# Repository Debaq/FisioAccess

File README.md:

# FisioAccess

Software para la toma de electrocardiograma

## Description

This project was created with PySide6 and Python.

## Author

- **Vanessa**
- Email: vanessauribe858@gmail.com
- Organization: Uach

## Version

1.0.0

## License

This project is under the MIT license.

## Project Structure

```
src/
├── config/        # Configuration files
├── ui/            # User interface components
│   ├── dialogs/   # Dialog windows
│   └── views/     # View components
├── models/        # Data models
└── utils/         # Utility functions

resources/
├── images/        # Images and icons
├── styles/        # Style sheets
├── icons/         # Application icons
└── translations/  # Language files
    ├── es.ts     # Spanish translation source
    ├── es.qm     # Compiled Spanish translation
    ├── en.ts     # English translation source
    └── en.qm     # Compiled English translation
```

## Requirements

- Python 3.12+
- PySide6
- Qt6 tools (for translations)
- Other dependencies in requirements.txt

## Installation

1. Clone the repository
2. Activate virtual environment: `source activate_env.sh`
3. Install dependencies: `pip install -r requirements.txt`
4. Compile translations: `./compile_translations.sh`

## Translations

### Adding a New Language

1. Create a new translation file (example for French):
   ```bash
   # Create fr.ts file in resources/translations/
   <?xml version="1.0" encoding="utf-8"?>
   <!DOCTYPE TS>
   <TS version="2.1" language="fr">
   <context>
       <name>MainWindow</name>
       <message>
           <source>Welcome to {}</source>
           <translation>Bienvenue à {}</translation>
       </message>
       <!-- Add more translations here -->
   </context>
   </TS>
   ```

2. Add the new language to compile_translations.sh:
   ```bash
    resources/translations/fr.ts -qm resources/translations/fr.qm
   ```

3. Compile translations:
   ```bash
   ./compile_translations.sh
   ```

### Creating Translation Files

The easiest way to create translation files is using Qt Linguist:

1. Install Qt6 Linguist:
   - Ubuntu/Debian: `sudo apt-get install qt6-tools-dev`
   - Fedora: `sudo dnf install qt6-linguist`
   - Arch: `sudo pacman -S qt6-tools`

2. Generate translation files:
   ```bash
   # Create/update .ts files
   lupdate-qt6 src/ -ts resources/translations/es.ts
   ```

3. Edit translations using Qt Linguist:
   ```bash
   linguist-qt6 resources/translations/es.ts
   ```

4. Compile translations:
   ```bash
   ./compile_translations.sh
   ```

## Building

To compile the project, run:

```bash
./compile.sh
```

## Usage

To run in development mode:

```bash
python src/main.py
```

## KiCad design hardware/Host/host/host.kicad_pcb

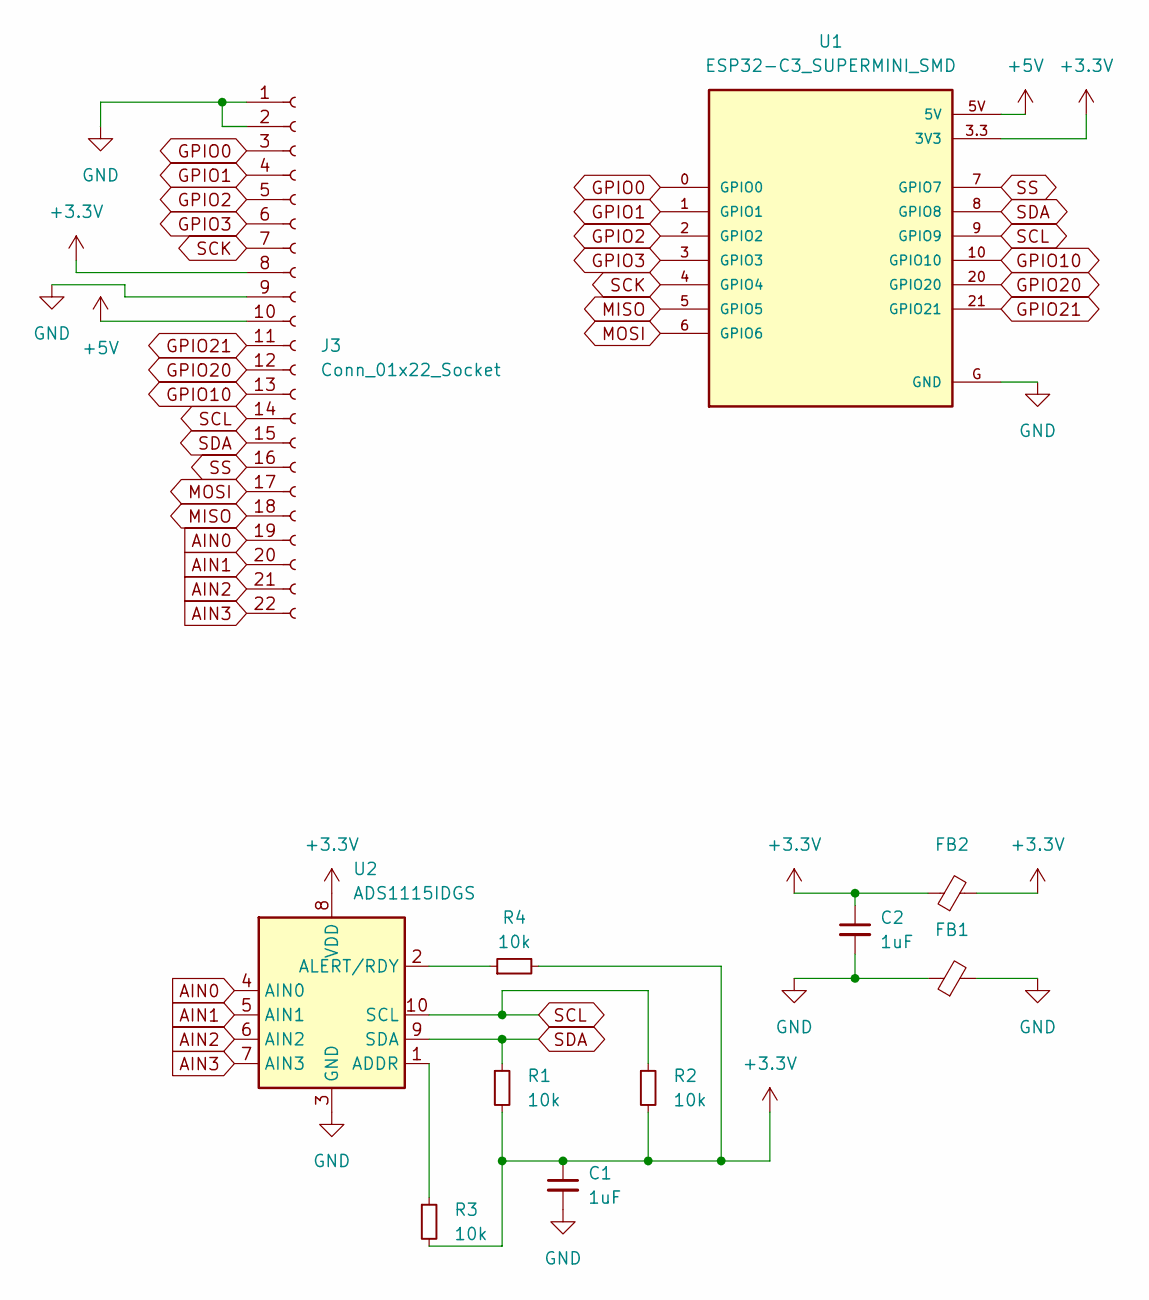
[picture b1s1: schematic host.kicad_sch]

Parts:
C1, C2: 1uF; C_1206_3216Metric_Pad1.33x1.80mm_HandSolder
FB1, FB2: L_1206_3216Metric_Pad1.22x1.90mm_HandSolder
J3: Conn_01x22_Socket; conn_board_host
R1, R2, R3, R4: 10k; R_1206_3216Metric_Pad1.30x1.75mm_HandSolder
U1: ESP32-C3_SUPERMINI_SMD; MODULE_ESP32-C3_SUPERMINI
U2: ADS1115IDGS; TSSOP-10_3x3mm_P0.5mm

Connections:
+3.3V: C1.1, C2.1, FB2.1, FB2.2, J3.8, R1.2, R2.2, R3.2, R4.2, U1.3.3 (3V3), U2.8 (VDD)
+5V: J3.10, U1.5V
AIN0: J3.19, U2.4 (AIN0)
AIN1: J3.20, U2.5 (AIN1)
AIN2: J3.21, U2.6 (AIN2)
AIN3: J3.22, U2.7 (AIN3)
GND: C1.2, C2.2, FB1.1, FB1.2, J3.1, J3.2, J3.9, U1.G (GND), U2.3 (GND)
GPIO0: J3.3, U1.0 (GPIO0)
GPIO1: J3.4, U1.1 (GPIO1)
GPIO2: J3.5, U1.2 (GPIO2)
GPIO3: J3.6, U1.3 (GPIO3)
GPIO10: J3.13, U1.10 (GPIO10)
GPIO20: J3.12, U1.20 (GPIO20)
GPIO21: J3.11, U1.21 (GPIO21)
MISO: J3.18, U1.5 (GPIO5)
MOSI: J3.17, U1.6 (GPIO6)
unnamed: R3.1, U2.1 (ADDR)
unnamed: R4.1, U2.2 (ALERT/RDY)
SCK: J3.7, U1.4 (GPIO4)
SCL: J3.14, R2.1, U1.9 (GPIO9), U2.10 (SCL)
SDA: J3.15, R1.1, U1.8 (GPIO8), U2.9 (SDA)
SS: J3.16, U1.7 (GPIO7)

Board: 2 copper layers, 11 parts (0 on the bottom side), 22 nets, no tracks yet.

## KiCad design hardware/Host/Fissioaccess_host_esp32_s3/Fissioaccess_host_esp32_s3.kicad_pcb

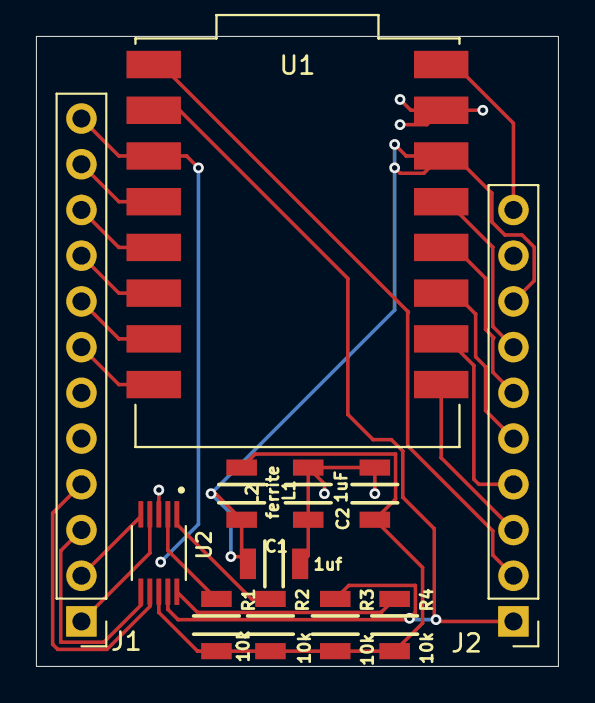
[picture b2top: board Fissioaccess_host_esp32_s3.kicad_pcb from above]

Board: 2 copper layers, 29.0 x 35.0 mm, 12 parts (0 on the bottom side), 23 nets.

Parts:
C1: 1uf; C_1206
C2: 1uF; C_1206
J1: PINHD_1x12; PinHeader_1x12_P2.54mm_Vertical
J2: PINHD_1x10; PinHeader_1x10_P2.54mm_Vertical
L1, L2: ferrite; C_1206
R1, R2, R3, R4: 10k; C_1206
U1: ESP32-C3; MODULE_ESP32-C3_SUPERMINI
U2: ADS; SOP50P490X110-10N

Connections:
+5V: J2.10, U1.5V
AIN0: J1.1, U2.4 (AIN0)
AIN1: J1.2, U2.5 (AIN1)
AIN2: J1.3, U2.6 (AIN2)
AIN3: J1.4, U2.7 (AIN3)
GND: C1.2, C2.2, J2.9, L1.1 (+), L1.2 (-), U1.G (GND), U2.3 (GND)
GPIO0: J2.3, U1.0 (GPIO0)
GPIO1: J2.4, U1.1 (GPIO1)
GPIO2: J2.5, U1.2 (GPIO2)
GPIO3: J2.6, U1.3 (GPIO3)
GPIO4: J2.7, U1.4 (GPIO4)
GPIO5: J2.2, U1.5 (GPIO5)
GPIO6: J2.1, R3.1, U1.6 (GPIO6), U2.9 (SDA)
GPIO7: J1.12, R4.1, U1.7 (GPIO7), U2.10 (SCL)
GPIO8: J1.11, U1.8 (GPIO8)
GPIO9: J1.10, U1.9 (GPIO9)
GPIO10: J1.9, U1.10 (GPIO10)
GPIO20: J1.8, U1.20 (GPIO20)
GPIO21: J1.7, U1.21 (GPIO21)
unnamed: R2.1, U2.1 (ADDR)
unnamed: R1.1, U2.2 (ALERT/RDY)
VCC: C1.1, J2.8, L2.2 (-), U1.3.3 (3V3)
VCC B: C2.1, L2.1 (+), R1.2, R2.2, R3.2, R4.2, U2.8 (VDD)

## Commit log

2024-07-25 cambios
2024-07-25 upgrade kivymd
2024-07-26 nuevos_para otra versión
2024-08-03 Add rst
2024-08-03 update help screen
2024-08-10 update rst and images
2024-08-12 mejoras para graficas
2024-08-13 rst update
2024-09-03 nuevo grafico
2024-09-10 nueva versión
2024-09-10 cambios v3
2024-09-18 logo
2024-09-18 cambios en la versión
2024-09-18 change in icons
2024-09-18 color in button
2024-09-19 cambios para funcionamiento del grafico
2024-09-20 marcadores
2024-09-21 funcionamiento correcto del toolbar
2024-09-21 limpieza de codigo pep8
2024-09-24 limpieza
2024-09-30 Create tree
2024-09-30 verificador de fb
2024-09-30 cierre fb
2024-09-30 firmware
2024-09-30 temp
2024-10-09 funcionamiento_puerto Serial
2024-10-09 cambios para serial
2024-10-09 ajuste de label serial
2024-10-09 funcionamiento en bind
2024-10-10 cambios otros
2024-10-14 connect_to_wifi
2024-10-14 cambio para web
2024-10-14 mejoras en el marcaje
2024-10-15 avance en la calibración
2025-03-31 Remove
2025-03-31 cambios menores
2025-03-31 cambios a versión piloto
    hemos cambiado la forma en que funcionará, pondremos todo en solo sistema, cuando se abra se levantará el servidor. abandonaremos por ahora el sistema embedido
2025-03-31 Update requirements
2025-04-02 add host hardware
2025-04-12 ni idea
2025-04-17 Update SerailDataHandler
2025-04-19 cambios a nueva versión
2025-04-20 exito al graficar al peo
2025-04-20 funcionando?
2025-04-20 cambios para activación de impresion serial
2025-04-20 pista
2025-04-20 filtros funcionando
2025-04-20 supercambios
2025-04-20 cambiios para extension maxima
2025-04-21 spin_fs funcional
2025-04-21 server del pico
